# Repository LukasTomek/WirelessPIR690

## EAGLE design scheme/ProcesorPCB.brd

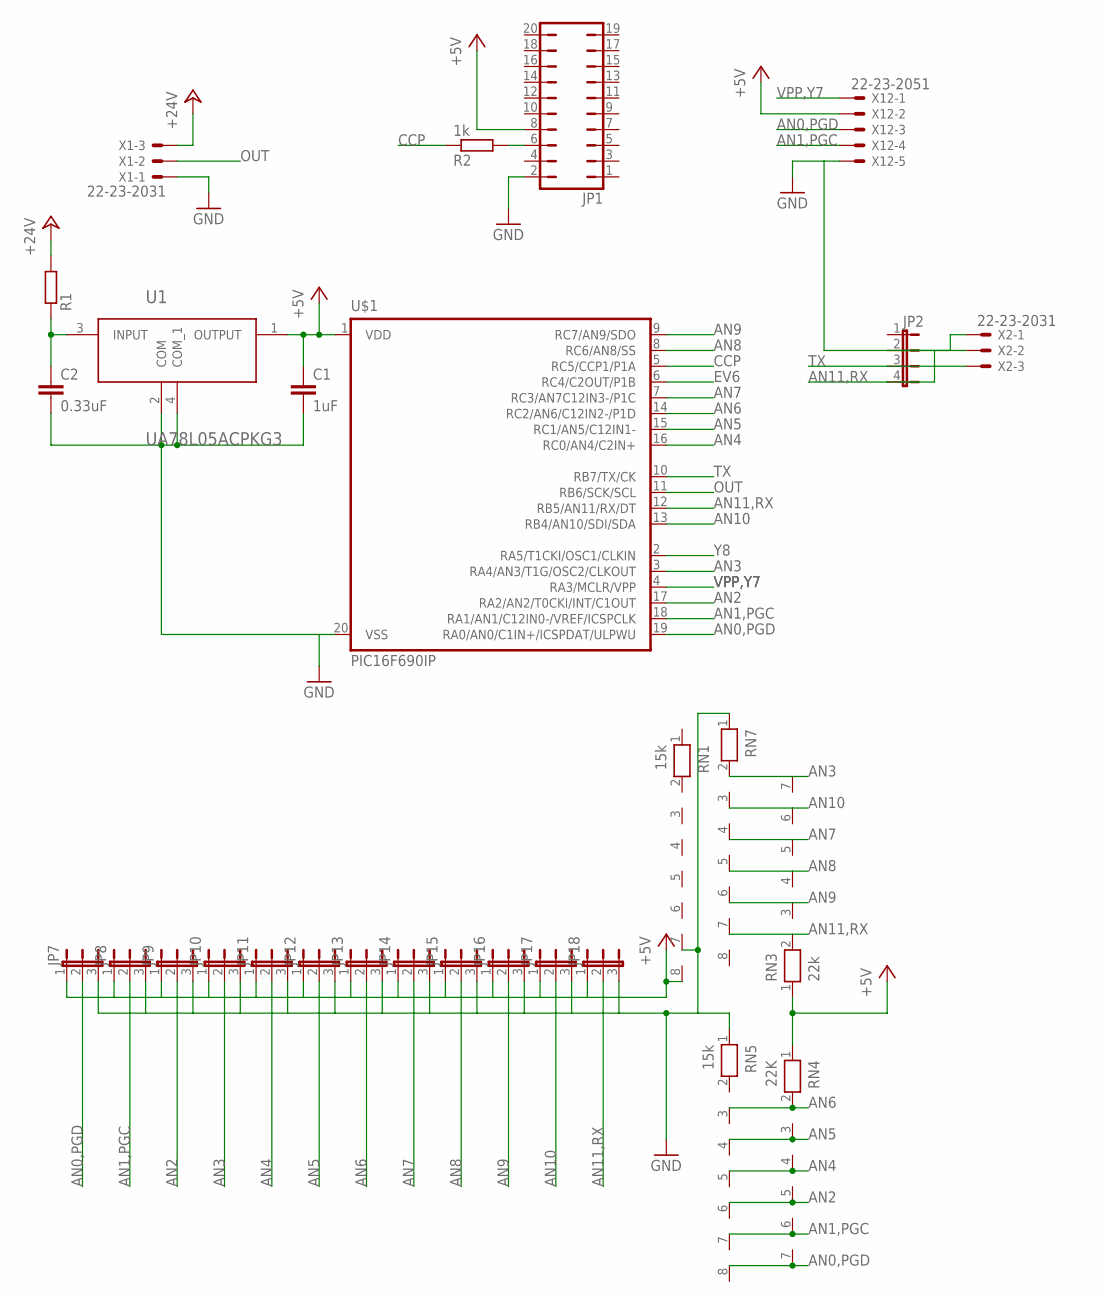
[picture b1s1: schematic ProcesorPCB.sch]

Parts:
C1: 1uF; C025-030X050
C2: 0.33uF; C025-030X050
JP1: JP10Q
JP2: JP4E; JP4
JP7, JP8, JP9, JP10, JP11, JP12, JP13, JP14, JP15, JP16, JP17, JP18: JP2E; JP2
R1: R-EU_0207/10; 0207/10
R2: 1k; 0204/7
RN1, RN5: 15k; RN-8
RN3: 22k; RN-7
RN4: 22K; RN-7
RN7: RN07; RN-8
U1: UA78L05ACPKG3; SOT150P400X160-4N
U$1: PIC16F690IP; DIL20
X1, X2: 22-23-2031
X12: 22-23-2051

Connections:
+5V: C1.1, JP1.8, JP7.1, JP8.1, JP9.1, JP10.1, JP11.1, JP12.1, JP13.1, JP14.1, JP15.1, JP16.1, JP17.1, JP18.1, RN1.8, RN3.1, RN4.1, U1.1 (OUTPUT), U$1.1 (VDD), X12.2
+24V: R1.2, X1.3
AN0,PGD: JP7.2, RN4.7, U$1.19 (RA0/AN0/C1IN+/ICSPDAT/ULPWU), X12.3
AN1,PGC: JP8.2, RN4.6, U$1.18 (RA1/AN1/C12IN0-/VREF/ICSPCLK), X12.4
AN2: JP9.2, RN4.5, U$1.17 (RA2/AN2/T0CKI/INT/C1OUT)
AN3: JP10.2, RN3.7, RN7.2, U$1.3 (RA4/AN3/T1G/OSC2/CLKOUT)
AN4: JP11.2, RN4.4, U$1.16 (RC0/AN4/C2IN+)
AN5: JP12.2, RN4.3, U$1.15 (RC1/AN5/C12IN1-)
AN6: JP13.2, RN4.2, U$1.14 (RC2/AN6/C12IN2-/P1D)
AN7: JP14.2, RN3.5, RN7.4, U$1.7 (RC3/AN7C12IN3-/P1C)
AN8: JP15.2, RN3.4, RN7.5, U$1.8 (RC6/AN8/SS)
AN9: JP16.2, RN3.3, RN7.6, U$1.9 (RC7/AN9/SDO)
AN10: JP17.2, RN3.6, RN7.3, U$1.13 (RB4/AN10/SDI/SDA)
AN11,RX: JP2.4, JP18.2, RN3.2, RN7.7, U$1.12 (RB5/AN11/RX/DT), X2.2
CCP: R2.1, U$1.5 (RC5/CCP1/P1A)
EV6: U$1.6 (RC4/C2OUT/P1B)
GND: C1.2, C2.2, JP1.2, JP2.2, JP7.3, JP8.3, JP9.3, JP10.3, JP11.3, JP12.3, JP13.3, JP14.3, JP15.3, JP16.3, JP17.3, JP18.3, RN1.7, RN5.1, RN7.1, U1.2 (COM), U1.4 (COM_1), U$1.20 (VSS), X1.1, X2.1, X12.5
unnamed: C2.1, R1.1, U1.3 (INPUT)
unnamed: JP1.6, R2.2
OUT: U$1.11 (RB6/SCK/SCL), X1.2
TX: JP2.3, U$1.10 (RB7/TX/CK), X2.3
VPP,Y7: U$1.4 (RA3/MCLR/VPP), X12.1
Y8: U$1.2 (RA5/T1CKI/OSC1/CLKIN)

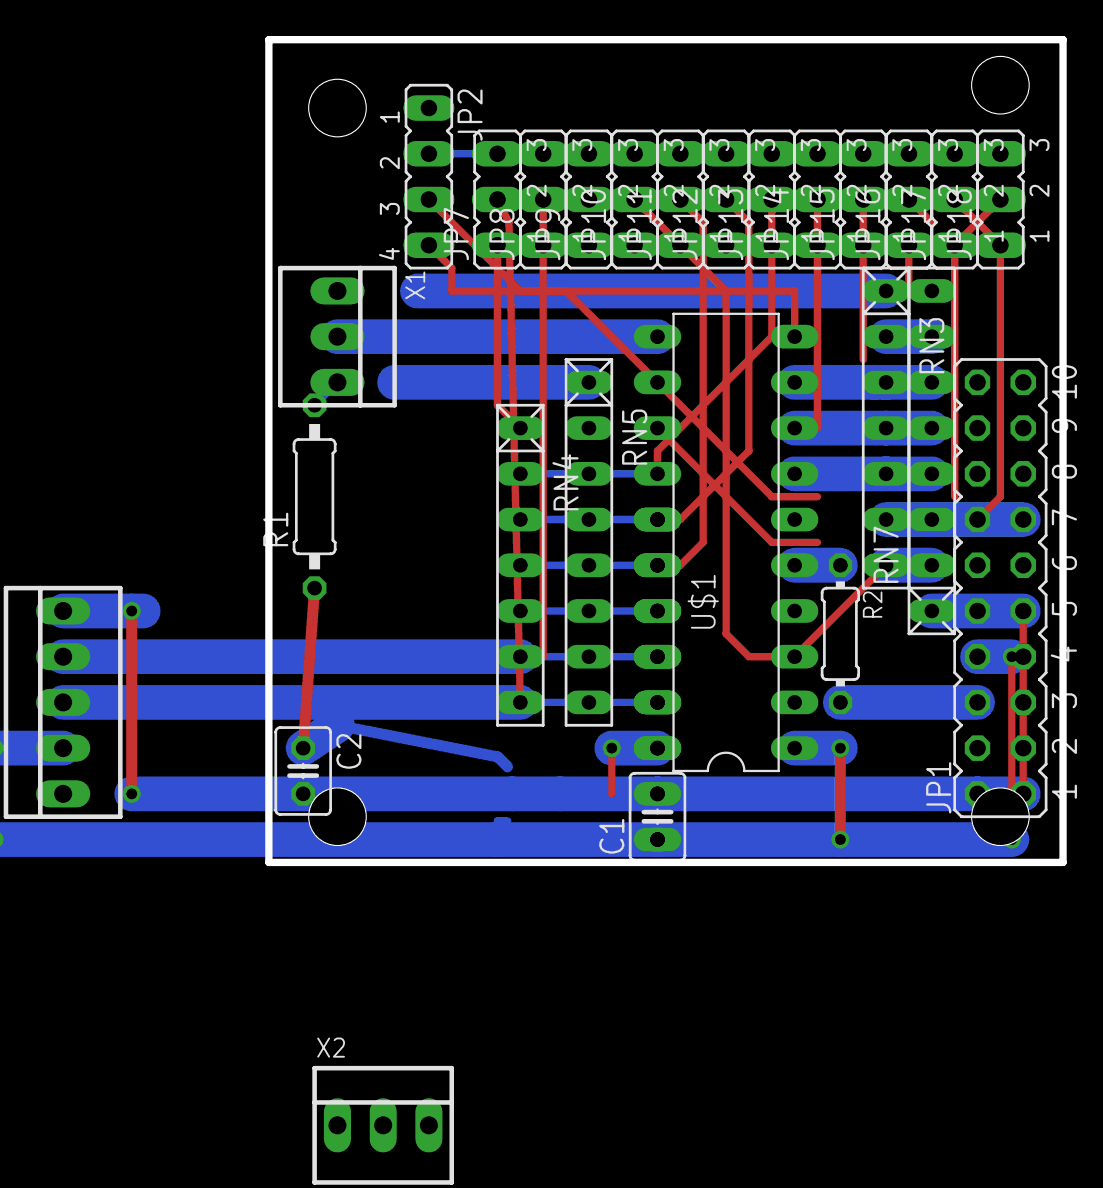
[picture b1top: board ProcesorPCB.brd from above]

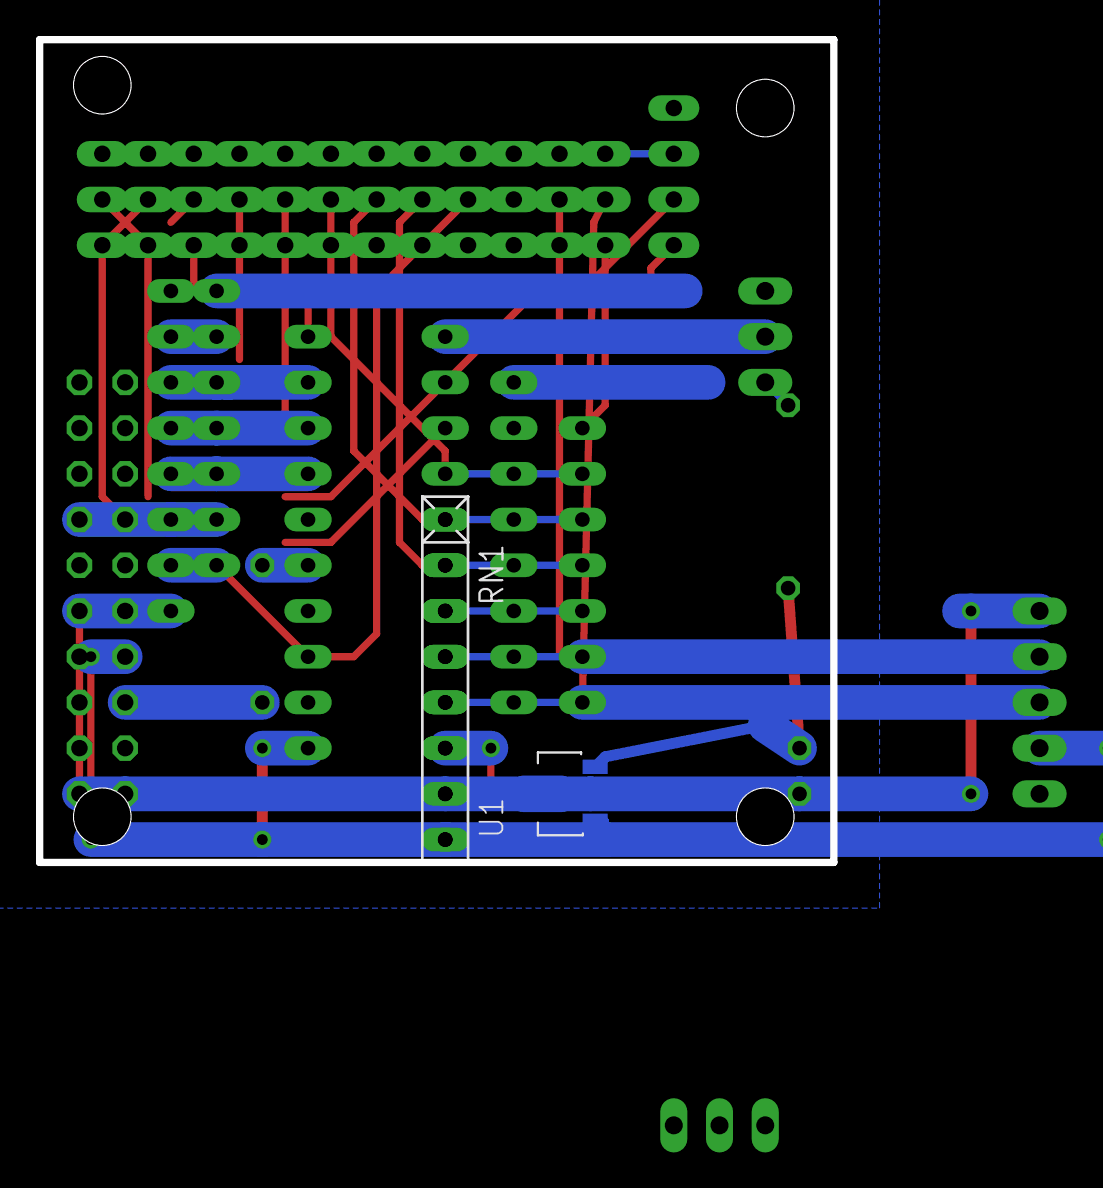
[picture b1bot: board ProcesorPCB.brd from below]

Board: 2 copper layers, 44.1 x 45.7 mm, 28 parts (2 on the bottom side), 21 nets.

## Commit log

2017-01-05 Test changes
2017-01-05 Test changes2
2017-01-06 test
2017-01-06 test2
2017-01-07 Test changes3
2017-01-07 Test changes4
2017-01-07 Test changes5
2017-01-08 Test time of execution
2017-01-08 Test changes6
2017-01-09 Test execution time
2017-01-09 Test changes7
2017-01-10 Test changes8
2017-01-10 Test changes9
2017-01-11 Preparation for test with tmr1 8bit for optimalization, and performace measurement.
2017-01-11 Separate string to str.c, add buffer overflow for timer0
2017-01-12 Test 8Byte timer1
2017-01-12 Timer1 8bit, write dec number to SP. Working test.
2017-01-12 Měření je pouze zakomentováno a výpis časů měření pulzů taky.
2017-01-12 Odstranění zakomentovaného kodu.
2017-01-13 First try to check for correct address
2017-01-15 Přidání dokumentace. Doplnění chceku oproti nastaveným hodnotám.
2017-01-18 Add out put
2017-01-18 Check primanych dat jestli odpovidajitem v paměti, není zcela funkční.
2017-01-20 Repair sp _send to buffer instead of waiting in loop.
2017-01-25 Plně funkční verze s blikající diodou.
2017-01-25 Add scheme of dev pcb board.
2017-02-05 Work on PCB
2017-02-05 Hmm not Saved
2017-02-07 PCB borad almost finished.
2017-02-13 Add documentation for LM358, update schema, add adc settings from previous project to file orig_mail.c
2017-02-16 Start working on Reading address by partically add adc conversion.
2017-02-16 Add Doc files missing in previous commit
2017-02-17 Next stage of address reading
2017-03-20 Added reading from adc for address settings.
